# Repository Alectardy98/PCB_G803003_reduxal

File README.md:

# GH80-3003 Reduxal

Open-sourced Cherry MX PCB using the Pi Pico (RP2040) for the Cherry G80 3001 line of keyboards. Stock keyboards shipped originally with Cherry MY switches.

Original Placement measurements taken from other open-sourced PCB designs.
https://github.com/evyd13/gh80-series
https://github.com/Gacathon/Chili

## Production
Production files in the JLCPCB Folder

## Firmware
Qmk/Vial Firmware in the firmware folder

Use at your own risk.

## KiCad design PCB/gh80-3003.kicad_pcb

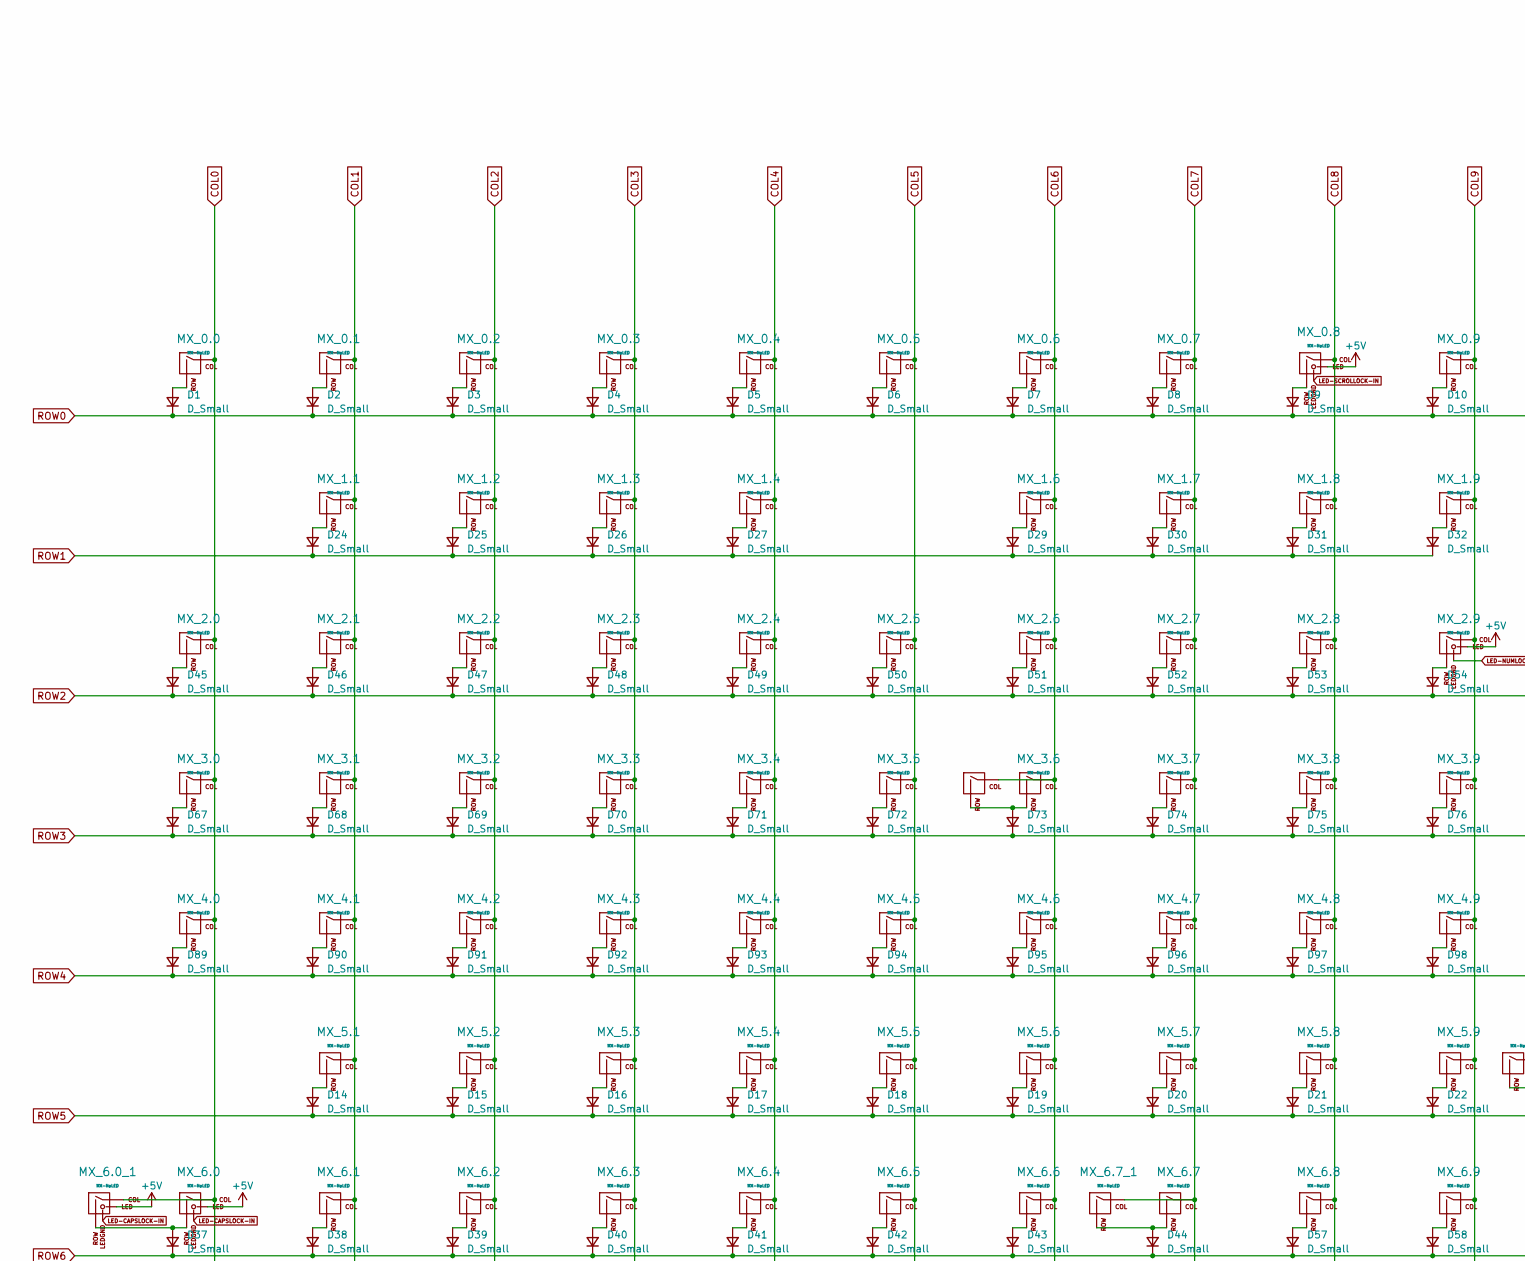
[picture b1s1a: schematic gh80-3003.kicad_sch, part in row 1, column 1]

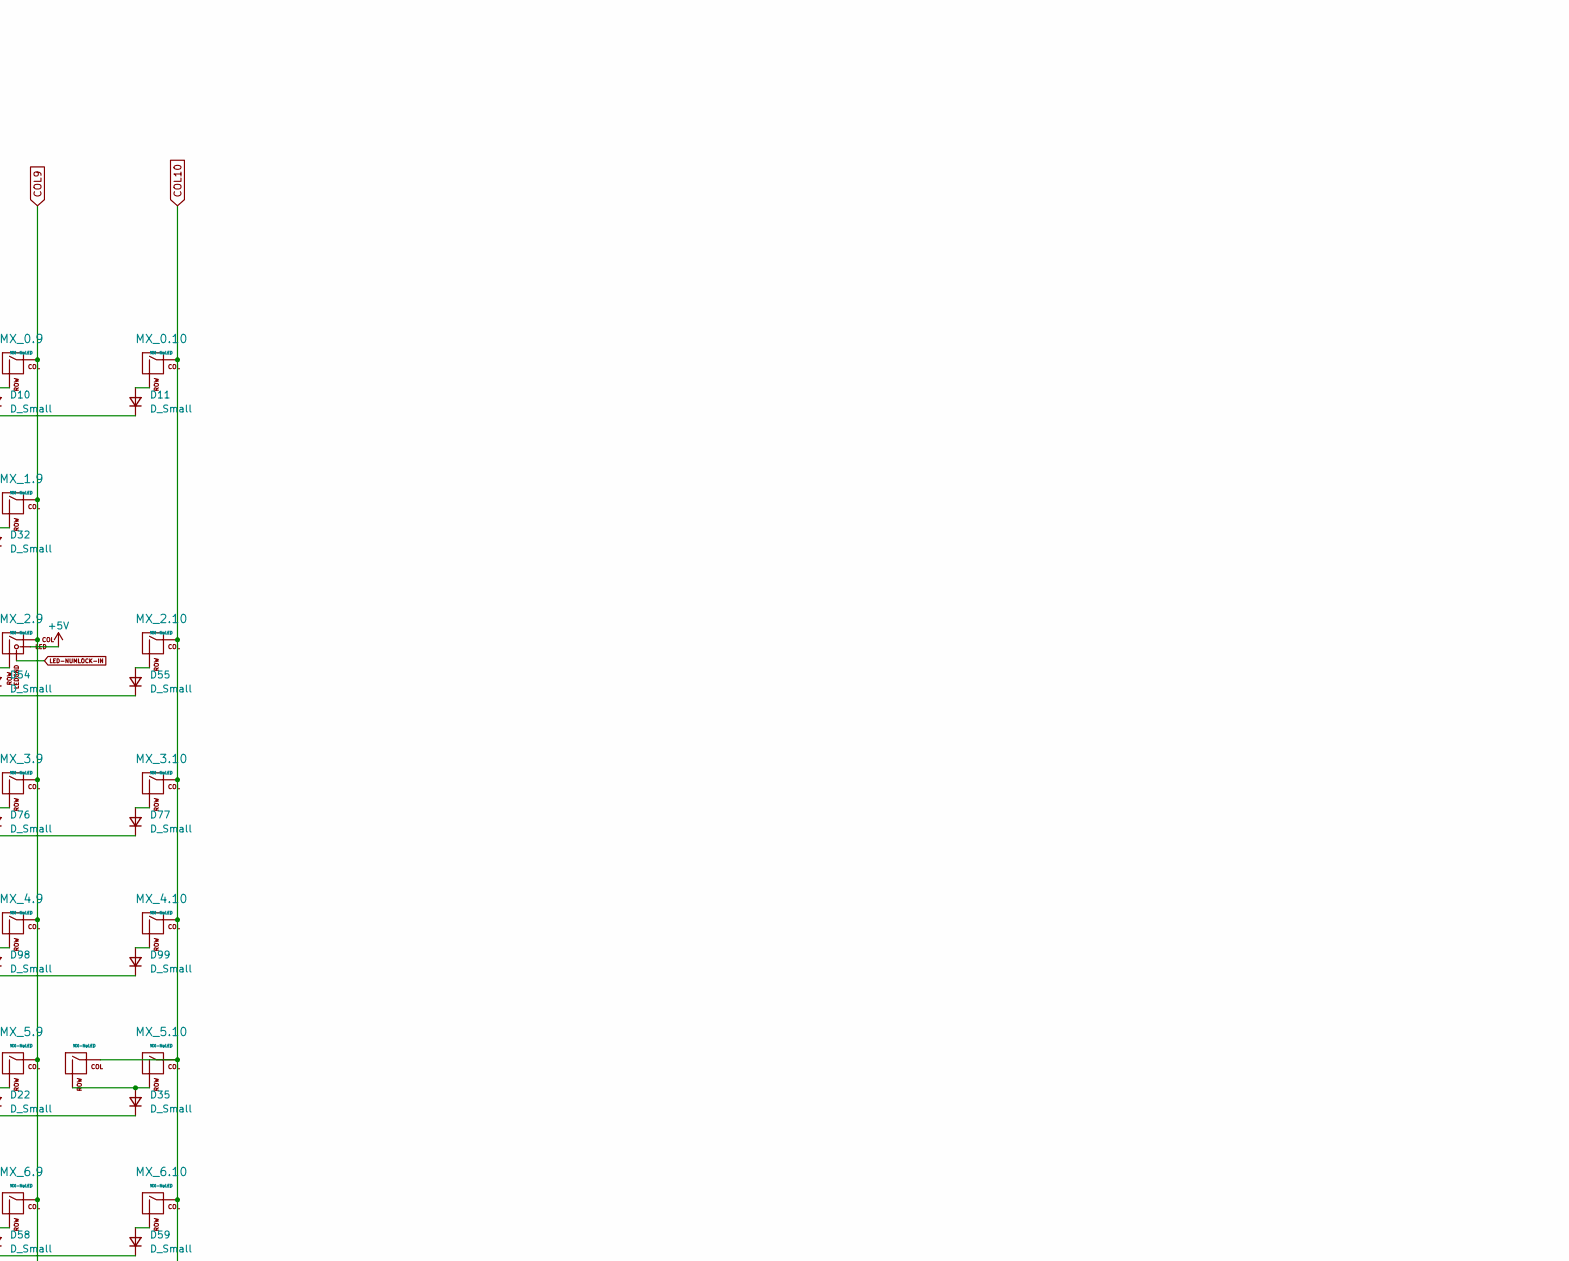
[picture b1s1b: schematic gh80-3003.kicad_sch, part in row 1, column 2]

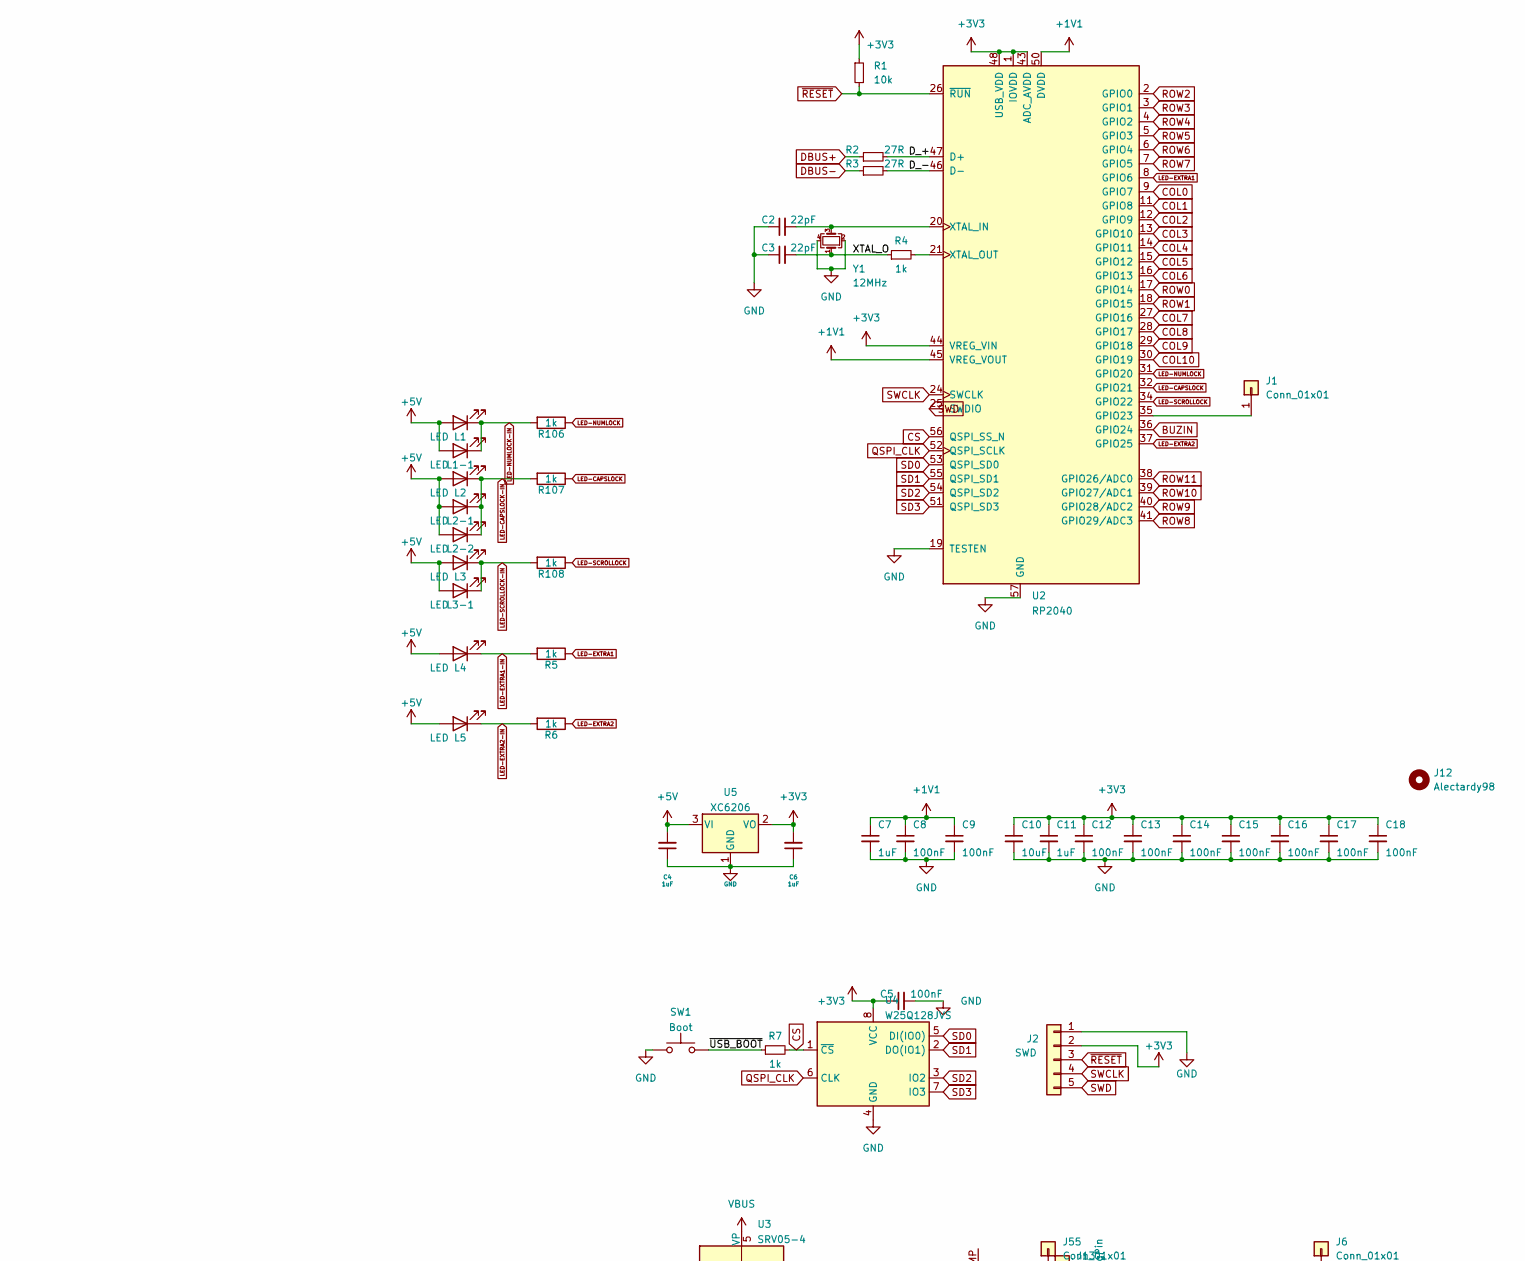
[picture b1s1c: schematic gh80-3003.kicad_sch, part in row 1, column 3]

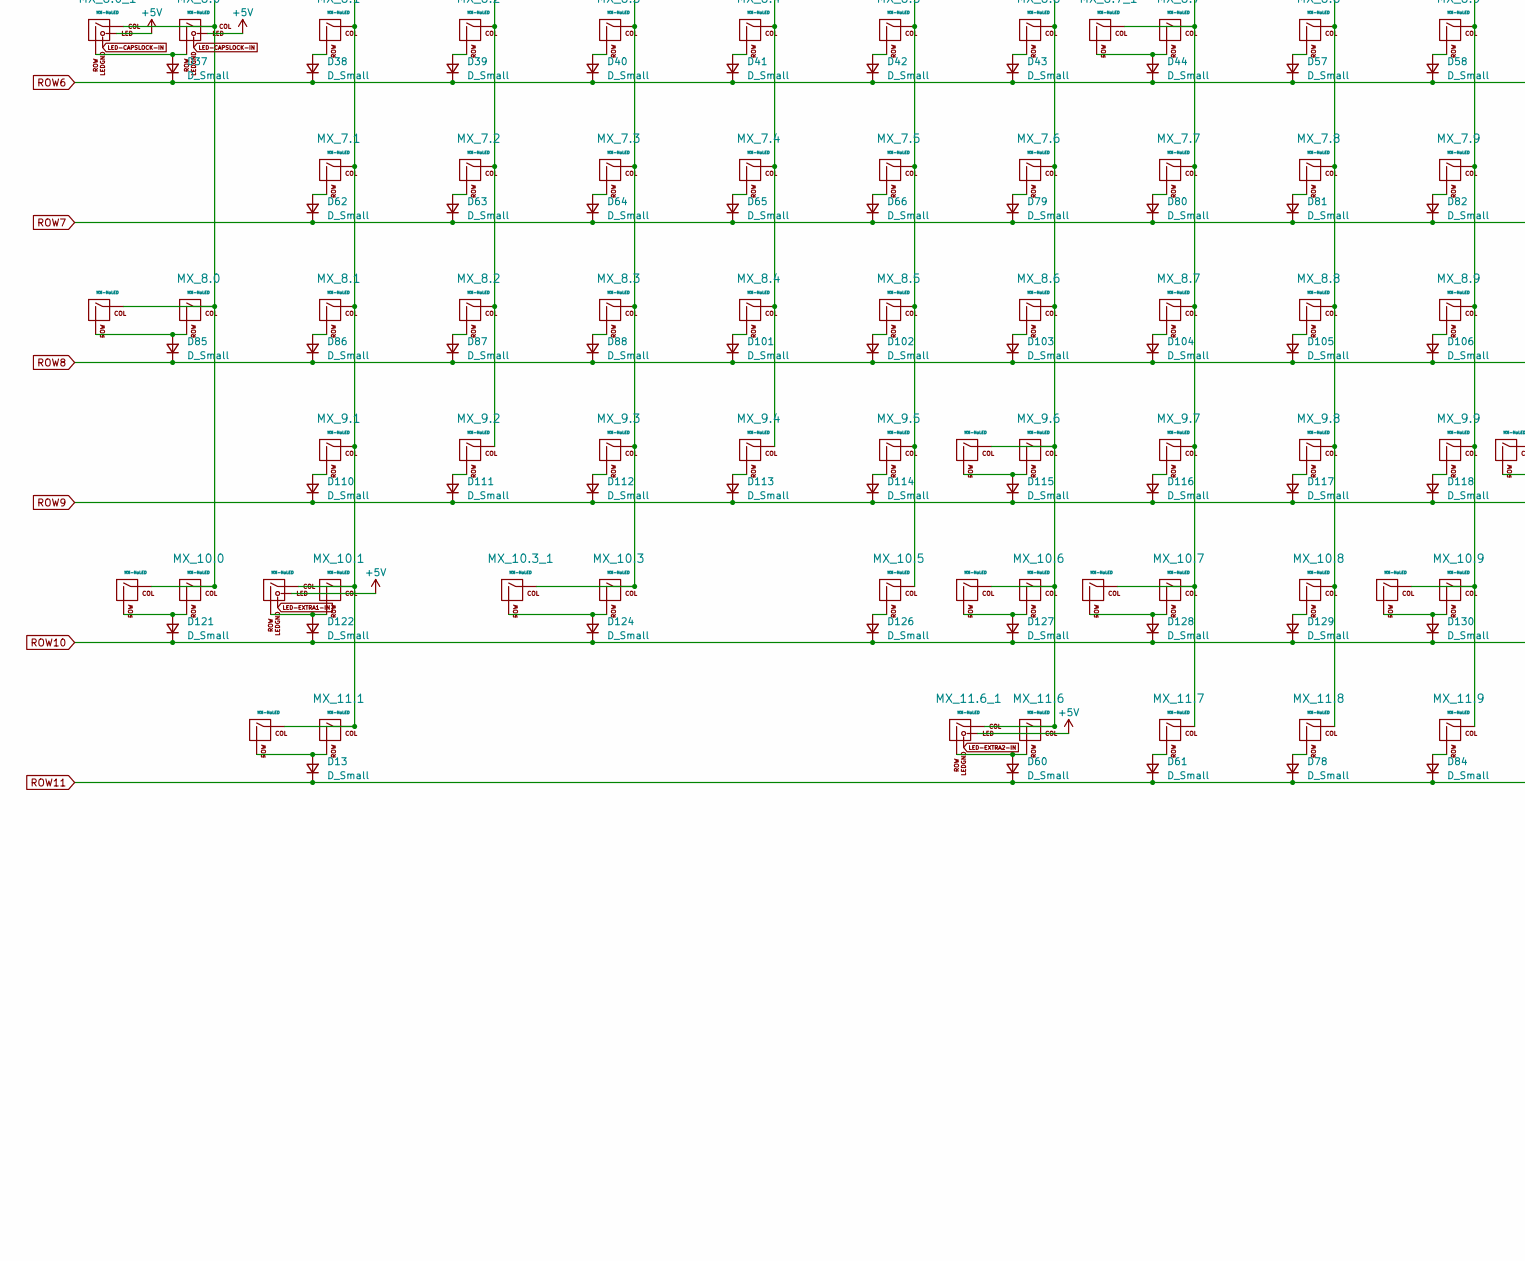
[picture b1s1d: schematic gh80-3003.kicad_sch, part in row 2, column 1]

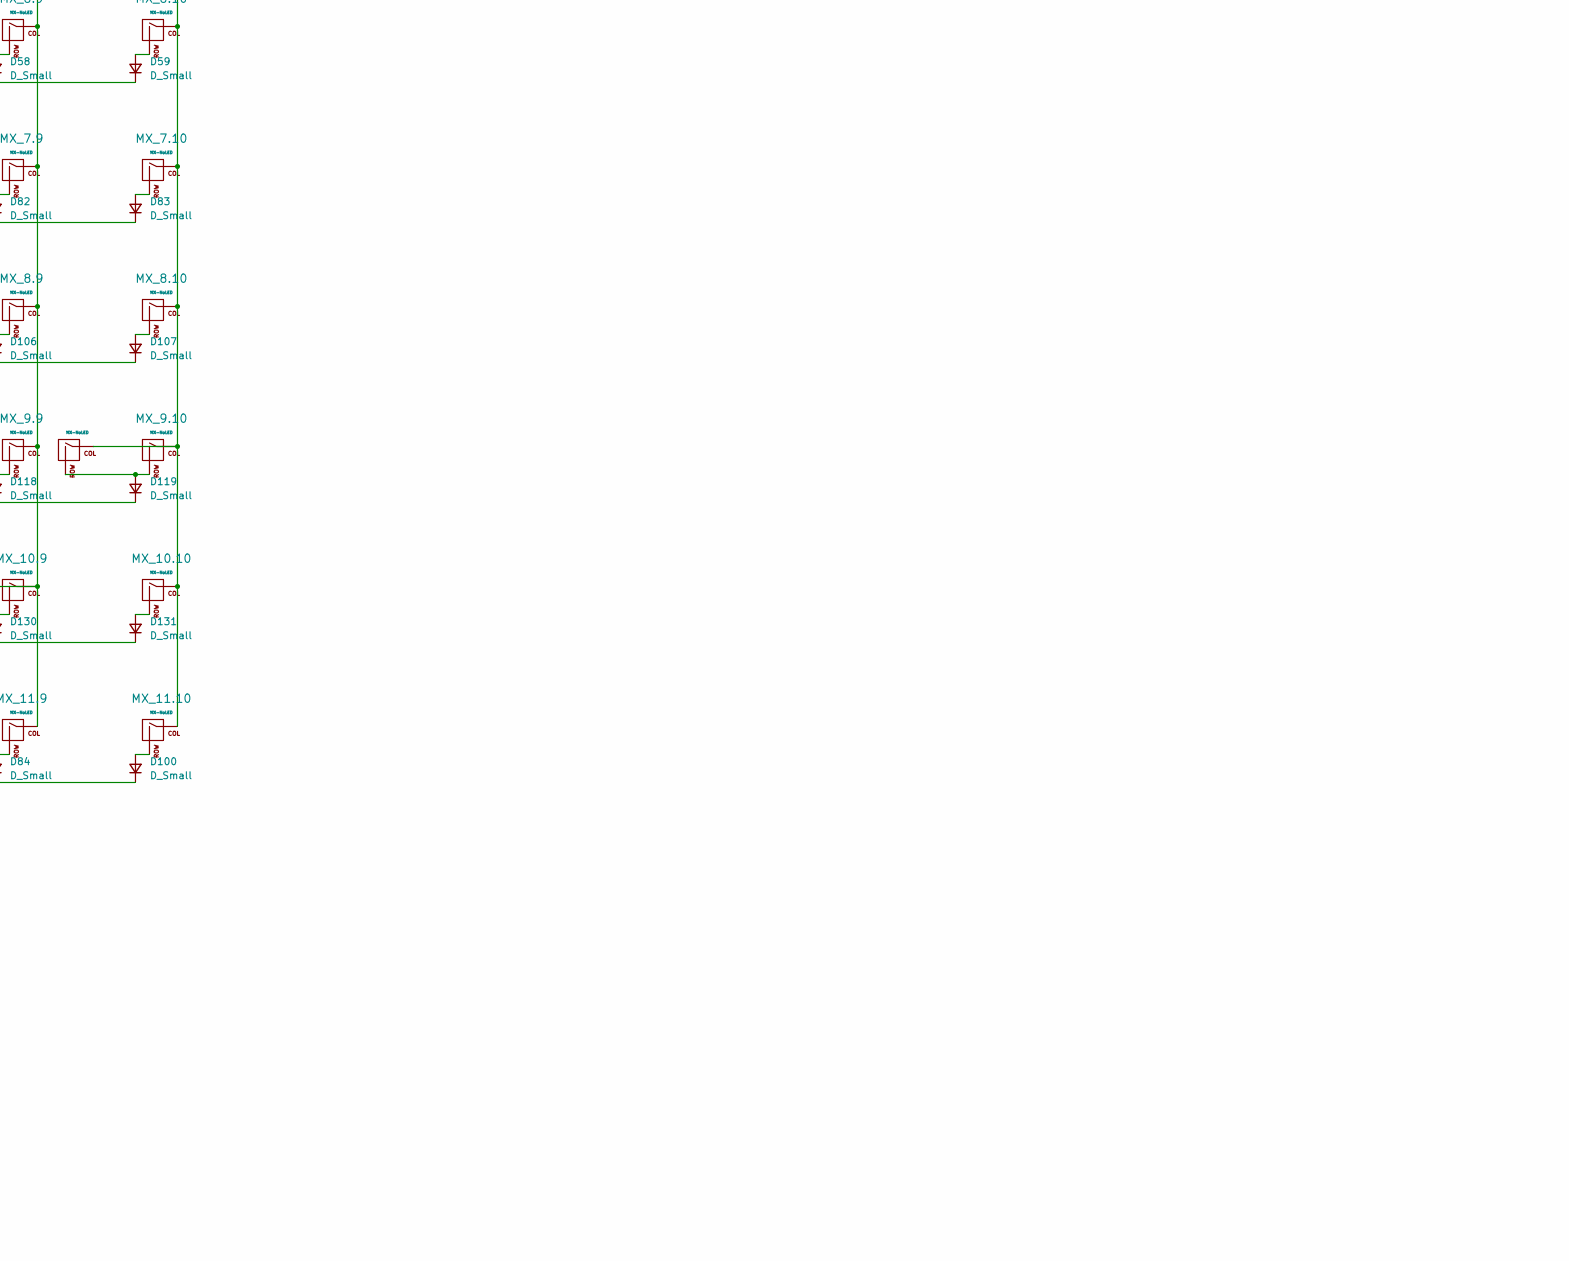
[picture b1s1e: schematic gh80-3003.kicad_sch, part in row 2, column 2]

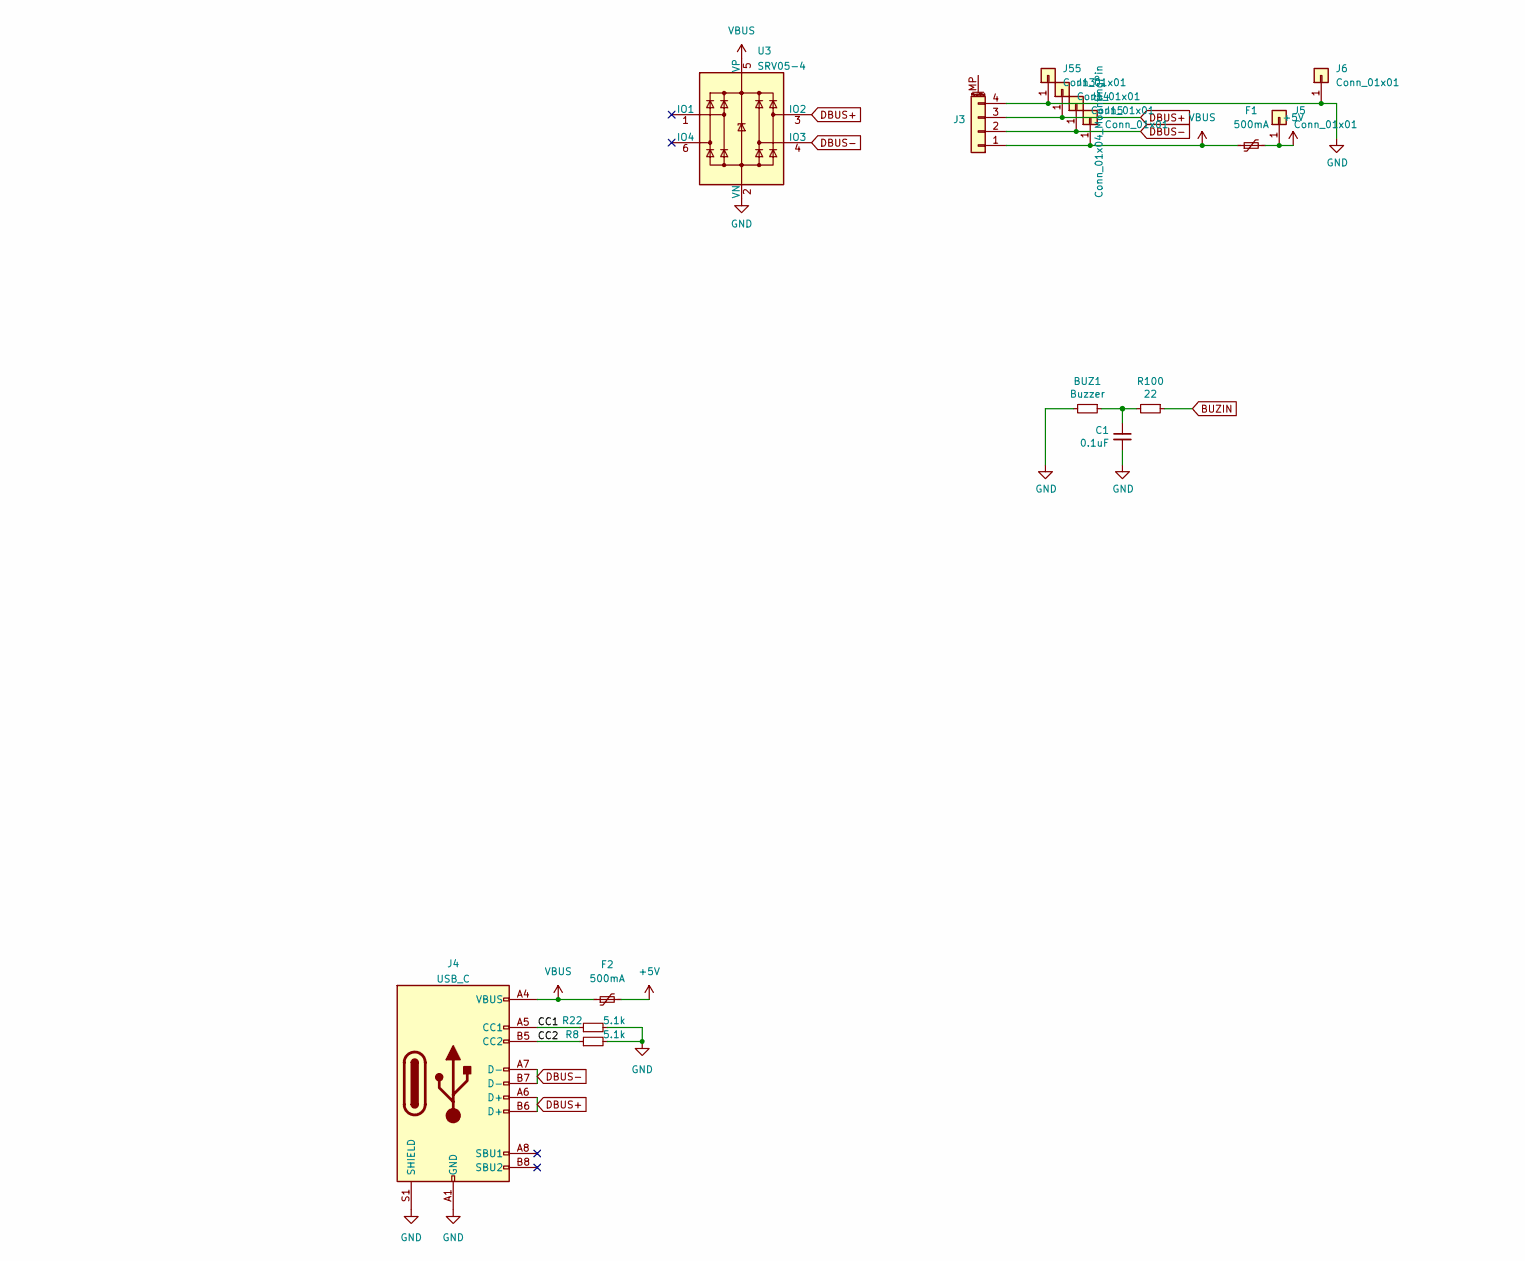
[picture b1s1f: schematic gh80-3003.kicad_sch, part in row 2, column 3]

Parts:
BUZ1: Buzzer; Buzzer_Mallory_AST1109MLTRQ
C1: 0.1uF; C_0805_2012Metric
C2, C3: 22pF; C_0402_1005Metric; LCSC C1555
C4, C6, C7, C11: 1uF; C_0402_1005Metric; LCSC C52923
C5, C8, C9, C12, C13, C14, C15, C16, C17, C18: 100nF; C_0402_1005Metric; LCSC C1525
C10: 10uF; C_0402_1005Metric; LCSC C15525
D1, D2, D3, D4, D5, D6, D7, D8, D9, D10, D11, D13, D14, D15, D16, D17, D18, D19, D20, D21, D22, D24, D25, D26, D27, D29, D30, D31, D32, D35, D37, D38, D39, D40, D41, D42, D43, D44, D45, D46, D47, D48, D49, D50, D51, D52, D53, D54, D55, D57, D58, D59, D60, D61, D62, D63, D64, D65, D66, D67, D68, D69, D70, D71, D72, D73, D74, D75, D76, D77, D78, D79, D80, D81, D82, D83, D84, D85, D86, D87, D88, D89, D90, D91, D92, D93, D94, D95, D96, D97, D98, D99, D100, D101, D102, D103, D104, D105, D106, D107, D110, D111, D112, D113, D114, D115, D116, D117, D118, D119, D121, D122, D124, D126, D127, D128, D129, D130, D131: D_Small; D_SOD-123
F1, F2: 500mA; Fuse_1206_3216Metric; LCSC C70076
J1, J5, J6, J13, J14, J15, J55: Conn_01x01; TestPoint_Plated_Hole_D2.0mm
J2: SWD; PinSocket_1x05_P2.54mm_Vertical
J3: Conn_01x04_MountingPin; JST_SH_SM04B-SRSS-TB_1x04-1MP_P1.00mm_Horizontal
J4: USB_C; USB_C_Receptacle_HRO_TYPE-C-31-M-12; LCSC C165948
J12: Alectardy98; Alectardy98101
L1, L2, L3: LED; LED_D3.0mm
L1-1, L2-1, L2-2, L3-1, L4, L5: LED; CHERRY_MX_LED
MX_0.0, MX_0.1, MX_0.2, MX_0.3, MX_0.4, MX_0.5, MX_0.6, MX_0.7, MX_0.9, MX_0.10, MX_1.1, MX_1.2, MX_1.3, MX_1.4, MX_1.6, MX_1.7, MX_1.8, MX_1.9, MX_2.0, MX_2.1, MX_2.2, MX_2.3, MX_2.4, MX_2.5, MX_2.6, MX_2.7, MX_2.8, MX_2.10, MX_3.0, MX_3.1, MX_3.2, MX_3.3, MX_3.4, MX_3.5, MX_3.6, MX_3.7, MX_3.8, MX_3.9, MX_3.10, MX_4.1, MX_4.2, MX_4.3, MX_4.4, MX_4.5, MX_4.6, MX_4.8, MX_4.9, MX_4.10, MX_5.1, MX_5.2, MX_5.3, MX_5.4, MX_5.5, MX_5.6, MX_5.7, MX_5.8, MX_5.9, MX_5.10, MX_6.1, MX_6.2, MX_6.3, MX_6.4, MX_6.5, MX_6.6, MX_6.8, MX_6.9, MX_6.10, MX_7.1, MX_7.2, MX_7.3, MX_7.4, MX_7.5, MX_7.6, MX_7.7, MX_7.8, MX_7.9, MX_7.10, MX_8.1, MX_8.2, MX_8.3, MX_8.4, MX_8.5, MX_8.6, MX_8.7, MX_8.8, MX_8.9, MX_8.10, MX_9.1, MX_9.2, MX_9.3, MX_9.4, MX_9.5, MX_9.7, MX_9.8, MX_9.9, MX_9.10, MX_10.8, MX_10.9, MX_10.10, MX_11.7, MX_11.8, MX_11.9, MX_11.10: MX-NoLED; MXOnly-1U-NoLED
MX_0.8, MX_2.9, MX_10.1_1, MX_11.6_1: MX-NoLED; MXOnly-1U
MX_3.6_1, MX_10.9_1: MX-NoLED; MXOnly-2U-NoLED
MX_4.0, MX_4.7, MX_10.0_1, MX_10.6_1, MX_10.7_1, MX_11.1_1: MX-NoLED; MXOnly-1.5U-NoLED
MX_5.10_1, MX_9.10_1: MX-NoLED; MXOnly-2U-VerticalStabilizers-NoLED
MX_6.0: MX-NoLED; MXOnly-1.75U
MX_6.0_1: MX-NoLED; MXOnly-1.25U
MX_6.7, MX_8.0_1: MX-NoLED; MXOnly-2.25U-NoLED
MX_6.7_1: MX-NoLED; MXOnly-ISO-ReversedStabilizers-NoLED
MX_8.0, MX_10.0, MX_10.1, MX_10.5, MX_10.6, MX_10.7, MX_11.1, MX_11.6: MX-NoLED; MXOnly-1.25U-NoLED
MX_9.6: MX-NoLED; MXOnly-1.75U-NoLED
MX_9.6_1: MX-NoLED; MXOnly-2.75U-NoLED
MX_10.3: MX-NoLED; MXOnly-6.25U-NoLED
MX_10.3_1: MX-NoLED; MXOnly-7U-NoLED
R1: 10k; R_0402_1005Metric; LCSC C25744
R2, R3: 27R; R_0603_1608Metric; LCSC C25190
R4, R7: 1k; R_0402_1005Metric; LCSC C11702
R5, R6, R106, R107, R108: 1k; R_0805_2012Metric
R8, R22: 5.1k; R_0402_1005Metric; LCSC C25905
R100: 22; R_0805_2012Metric
SW1: Boot; PinSocket_1x02_P2.54mm_Vertical
U2: RP2040; RP2040-QFN-56; LCSC C2040
U3: SRV05-4; SOT-23-6-routable; LCSC C85364
U4: W25Q128JVS; SOIC-8_5.23x5.23mm_P1.27mm; LCSC C97521
U5: XC6206; SOT-23; LCSC C5446
Y1: 12MHz; Crystal_SMD_3225-4Pin_3.2x2.5mm; LCSC C9002

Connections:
+1V1: C7.1, C8.1, C9.1, U2.23 (DVDD), U2.45 (VREG_VOUT), U2.50 (DVDD)
+3V3: C5.1, C6.2, C10.1, C11.1, C12.1, C13.1, C14.1, C15.1, C16.1, C17.1, C18.1, J2.2, R1.1, U2.1 (IOVDD), U2.10 (IOVDD), U2.22 (IOVDD), U2.33 (IOVDD), U2.42 (IOVDD), U2.43 (ADC_AVDD), U2.44 (VREG_VIN), U2.48 (USB_VDD), U2.49 (IOVDD), U4.8 (VCC), U5.2 (VO)
+5V: C4.2, F1.2, F2.2, J5.1, L1.2 (A), L1-1.2 (A), L2.2 (A), L2-1.2 (A), L2-2.2 (A), L3.2 (A), L3-1.2 (A), L4.2 (A), L5.2 (A), MX_0.8.3 (LED), MX_2.9.3 (LED), MX_6.0.3 (LED), MX_6.0_1.3 (LED), MX_10.1_1.3 (LED), MX_11.6_1.3 (LED), U5.3 (VI)
/CC1: J4.A5 (CC1), R22.1
/CC2: J4.B5 (CC2), R8.1
/D_+: R2.2, U2.47 (D+)
/D_-: R3.2, U2.46 (D-)
/XTAL_O: C3.2, R4.1, Y1.1
/~USB_BOOT: R7.1, SW1.2
BUZIN: R100.1, U2.36 (GPIO24)
COL0: MX_0.0.1 (COL), MX_2.0.1 (COL), MX_3.0.1 (COL), MX_4.0.1 (COL), MX_6.0.1 (COL), MX_6.0_1.1 (COL), MX_8.0.1 (COL), MX_8.0_1.1 (COL), MX_10.0.1 (COL), MX_10.0_1.1 (COL), U2.9 (GPIO7)
COL1: MX_0.1.1 (COL), MX_1.1.1 (COL), MX_2.1.1 (COL), MX_3.1.1 (COL), MX_4.1.1 (COL), MX_5.1.1 (COL), MX_6.1.1 (COL), MX_7.1.1 (COL), MX_8.1.1 (COL), MX_9.1.1 (COL), MX_10.1.1 (COL), MX_10.1_1.1 (COL), MX_11.1.1 (COL), MX_11.1_1.1 (COL), U2.11 (GPIO8)
COL2: MX_0.2.1 (COL), MX_1.2.1 (COL), MX_2.2.1 (COL), MX_3.2.1 (COL), MX_4.2.1 (COL), MX_5.2.1 (COL), MX_6.2.1 (COL), MX_7.2.1 (COL), MX_8.2.1 (COL), MX_9.2.1 (COL), U2.12 (GPIO9)
COL3: MX_0.3.1 (COL), MX_1.3.1 (COL), MX_2.3.1 (COL), MX_3.3.1 (COL), MX_4.3.1 (COL), MX_5.3.1 (COL), MX_6.3.1 (COL), MX_7.3.1 (COL), MX_8.3.1 (COL), MX_9.3.1 (COL), MX_10.3.1 (COL), MX_10.3_1.1 (COL), U2.13 (GPIO10)
COL4: MX_0.4.1 (COL), MX_1.4.1 (COL), MX_2.4.1 (COL), MX_3.4.1 (COL), MX_4.4.1 (COL), MX_5.4.1 (COL), MX_6.4.1 (COL), MX_7.4.1 (COL), MX_8.4.1 (COL), MX_9.4.1 (COL), U2.14 (GPIO11)
COL5: MX_0.5.1 (COL), MX_2.5.1 (COL), MX_3.5.1 (COL), MX_4.5.1 (COL), MX_5.5.1 (COL), MX_6.5.1 (COL), MX_7.5.1 (COL), MX_8.5.1 (COL), MX_9.5.1 (COL), MX_10.5.1 (COL), U2.15 (GPIO12)
COL6: MX_0.6.1 (COL), MX_1.6.1 (COL), MX_2.6.1 (COL), MX_3.6.1 (COL), MX_3.6_1.1 (COL), MX_4.6.1 (COL), MX_5.6.1 (COL), MX_6.6.1 (COL), MX_7.6.1 (COL), MX_8.6.1 (COL), MX_9.6.1 (COL), MX_9.6_1.1 (COL), MX_10.6.1 (COL), MX_10.6_1.1 (COL), MX_11.6.1 (COL), MX_11.6_1.1 (COL), U2.16 (GPIO13)
COL7: MX_0.7.1 (COL), MX_1.7.1 (COL), MX_2.7.1 (COL), MX_3.7.1 (COL), MX_4.7.1 (COL), MX_5.7.1 (COL), MX_6.7.1 (COL), MX_6.7_1.1 (COL), MX_7.7.1 (COL), MX_8.7.1 (COL), MX_9.7.1 (COL), MX_10.7.1 (COL), MX_10.7_1.1 (COL), MX_11.7.1 (COL), U2.27 (GPIO16)
COL8: MX_0.8.1 (COL), MX_1.8.1 (COL), MX_2.8.1 (COL), MX_3.8.1 (COL), MX_4.8.1 (COL), MX_5.8.1 (COL), MX_6.8.1 (COL), MX_7.8.1 (COL), MX_8.8.1 (COL), MX_9.8.1 (COL), MX_10.8.1 (COL), MX_11.8.1 (COL), U2.28 (GPIO17)
COL9: MX_0.9.1 (COL), MX_1.9.1 (COL), MX_2.9.1 (COL), MX_3.9.1 (COL), MX_4.9.1 (COL), MX_5.9.1 (COL), MX_6.9.1 (COL), MX_7.9.1 (COL), MX_8.9.1 (COL), MX_9.9.1 (COL), MX_10.9.1 (COL), MX_10.9_1.1 (COL), MX_11.9.1 (COL), U2.29 (GPIO18)
COL10: MX_0.10.1 (COL), MX_2.10.1 (COL), MX_3.10.1 (COL), MX_4.10.1 (COL), MX_5.10.1 (COL), MX_5.10_1.1 (COL), MX_6.10.1 (COL), MX_7.10.1 (COL), MX_8.10.1 (COL), MX_9.10.1 (COL), MX_9.10_1.1 (COL), MX_10.10.1 (COL), MX_11.10.1 (COL), U2.30 (GPIO19)
CS: R7.2, U2.56 (QSPI_SS_N), U4.1 (~CS)
DBUS+: J3.3, J4.A6 (D+), J4.B6 (D+), J13.1, R2.1, U3.3 (IO2)
DBUS-: J3.2, J4.A7 (D-), J4.B7 (D-), J14.1, R3.1, U3.4 (IO3)
GND: BUZ1.2, C1.2, C2.1, C3.1, C4.1, C5.2, C6.1, C7.2, C8.2, C9.2, C10.2, C11.2, C12.2, C13.2, C14.2, C15.2, C16.2, C17.2, C18.2, J2.1, J3.4, J4.A1 (GND), J4.A12 (GND), J4.B1 (GND), J4.B12 (GND), J4.S1 (SHIELD), J6.1, J55.1, R8.2, R22.2, SW1.1, U2.19 (TESTEN), U2.57 (GND), U3.2 (VN), U4.4 (GND), U5.1 (GND), Y1.2, Y1.4
LED-CAPSLOCK: R107.1, U2.32 (GPIO21)
LED-CAPSLOCK-IN: L2.1 (K), L2-1.1 (K), L2-2.1 (K), MX_6.0.4 (LEDGND), MX_6.0_1.4 (LEDGND), R107.2
LED-EXTRA1: R5.1, U2.8 (GPIO6)
LED-EXTRA1-IN: L4.1 (K), MX_10.1_1.4 (LEDGND), R5.2
LED-EXTRA2: R6.1, U2.37 (GPIO25)
LED-EXTRA2-IN: L5.1 (K), MX_11.6_1.4 (LEDGND), R6.2
LED-NUMLOCK: R106.1, U2.31 (GPIO20)
LED-NUMLOCK-IN: L1.1 (K), L1-1.1 (K), MX_2.9.4 (LEDGND), R106.2
LED-SCROLLOCK: R108.1, U2.34 (GPIO22)
LED-SCROLLOCK-IN: L3.1 (K), L3-1.1 (K), MX_0.8.4 (LEDGND), R108.2
unnamed: BUZ1.1, C1.1, R100.2
unnamed: D1.2 (A), MX_0.0.2 (ROW)
unnamed: D2.2 (A), MX_0.1.2 (ROW)
unnamed: D3.2 (A), MX_0.2.2 (ROW)
unnamed: D4.2 (A), MX_0.3.2 (ROW)
unnamed: D5.2 (A), MX_0.4.2 (ROW)
unnamed: D6.2 (A), MX_0.5.2 (ROW)
unnamed: D7.2 (A), MX_0.6.2 (ROW)
unnamed: D8.2 (A), MX_0.7.2 (ROW)
unnamed: D9.2 (A), MX_0.8.2 (ROW)
unnamed: D10.2 (A), MX_0.9.2 (ROW)
unnamed: D11.2 (A), MX_0.10.2 (ROW)
unnamed: D13.2 (A), MX_11.1.2 (ROW), MX_11.1_1.2 (ROW)
unnamed: D14.2 (A), MX_5.1.2 (ROW)
unnamed: D15.2 (A), MX_5.2.2 (ROW)
unnamed: D16.2 (A), MX_5.3.2 (ROW)
unnamed: D17.2 (A), MX_5.4.2 (ROW)
unnamed: D18.2 (A), MX_5.5.2 (ROW)
unnamed: D19.2 (A), MX_5.6.2 (ROW)
unnamed: D20.2 (A), MX_5.7.2 (ROW)
unnamed: D21.2 (A), MX_5.8.2 (ROW)
unnamed: D22.2 (A), MX_5.9.2 (ROW)
unnamed: D24.2 (A), MX_1.1.2 (ROW)
unnamed: D25.2 (A), MX_1.2.2 (ROW)
unnamed: D26.2 (A), MX_1.3.2 (ROW)
unnamed: D27.2 (A), MX_1.4.2 (ROW)
unnamed: D29.2 (A), MX_1.6.2 (ROW)
unnamed: D30.2 (A), MX_1.7.2 (ROW)
unnamed: D31.2 (A), MX_1.8.2 (ROW)
unnamed: D32.2 (A), MX_1.9.2 (ROW)
unnamed: D35.2 (A), MX_5.10.2 (ROW), MX_5.10_1.2 (ROW)
unnamed: D37.2 (A), MX_6.0.2 (ROW), MX_6.0_1.2 (ROW)
unnamed: D38.2 (A), MX_6.1.2 (ROW)
unnamed: D39.2 (A), MX_6.2.2 (ROW)
unnamed: D40.2 (A), MX_6.3.2 (ROW)
unnamed: D41.2 (A), MX_6.4.2 (ROW)
unnamed: D42.2 (A), MX_6.5.2 (ROW)
unnamed: D43.2 (A), MX_6.6.2 (ROW)
unnamed: D44.2 (A), MX_6.7.2 (ROW), MX_6.7_1.2 (ROW)
unnamed: D45.2 (A), MX_2.0.2 (ROW)
unnamed: D46.2 (A), MX_2.1.2 (ROW)
unnamed: D47.2 (A), MX_2.2.2 (ROW)
unnamed: D48.2 (A), MX_2.3.2 (ROW)
unnamed: D49.2 (A), MX_2.4.2 (ROW)
unnamed: D50.2 (A), MX_2.5.2 (ROW)
unnamed: D51.2 (A), MX_2.6.2 (ROW)
unnamed: D52.2 (A), MX_2.7.2 (ROW)
unnamed: D53.2 (A), MX_2.8.2 (ROW)
unnamed: D54.2 (A), MX_2.9.2 (ROW)
unnamed: D55.2 (A), MX_2.10.2 (ROW)
unnamed: D57.2 (A), MX_6.8.2 (ROW)
unnamed: D58.2 (A), MX_6.9.2 (ROW)
unnamed: D59.2 (A), MX_6.10.2 (ROW)
unnamed: D60.2 (A), MX_11.6.2 (ROW), MX_11.6_1.2 (ROW)
unnamed: D61.2 (A), MX_11.7.2 (ROW)
unnamed: D62.2 (A), MX_7.1.2 (ROW)
unnamed: D63.2 (A), MX_7.2.2 (ROW)
unnamed: D64.2 (A), MX_7.3.2 (ROW)
unnamed: D65.2 (A), MX_7.4.2 (ROW)
unnamed: D66.2 (A), MX_7.5.2 (ROW)
unnamed: D67.2 (A), MX_3.0.2 (ROW)
unnamed: D68.2 (A), MX_3.1.2 (ROW)
unnamed: D69.2 (A), MX_3.2.2 (ROW)
unnamed: D70.2 (A), MX_3.3.2 (ROW)
unnamed: D71.2 (A), MX_3.4.2 (ROW)
unnamed: D72.2 (A), MX_3.5.2 (ROW)
unnamed: D73.2 (A), MX_3.6.2 (ROW), MX_3.6_1.2 (ROW)
unnamed: D74.2 (A), MX_3.7.2 (ROW)
unnamed: D75.2 (A), MX_3.8.2 (ROW)
unnamed: D76.2 (A), MX_3.9.2 (ROW)
unnamed: D77.2 (A), MX_3.10.2 (ROW)
unnamed: D78.2 (A), MX_11.8.2 (ROW)
unnamed: D79.2 (A), MX_7.6.2 (ROW)
unnamed: D80.2 (A), MX_7.7.2 (ROW)
unnamed: D81.2 (A), MX_7.8.2 (ROW)
unnamed: D82.2 (A), MX_7.9.2 (ROW)
unnamed: D83.2 (A), MX_7.10.2 (ROW)
unnamed: D84.2 (A), MX_11.9.2 (ROW)
unnamed: D85.2 (A), MX_8.0.2 (ROW), MX_8.0_1.2 (ROW)
unnamed: D86.2 (A), MX_8.1.2 (ROW)
unnamed: D87.2 (A), MX_8.2.2 (ROW)
unnamed: D88.2 (A), MX_8.3.2 (ROW)
unnamed: D89.2 (A), MX_4.0.2 (ROW)
unnamed: D90.2 (A), MX_4.1.2 (ROW)
unnamed: D91.2 (A), MX_4.2.2 (ROW)
unnamed: D92.2 (A), MX_4.3.2 (ROW)
unnamed: D93.2 (A), MX_4.4.2 (ROW)
unnamed: D94.2 (A), MX_4.5.2 (ROW)
unnamed: D95.2 (A), MX_4.6.2 (ROW)
unnamed: D96.2 (A), MX_4.7.2 (ROW)
unnamed: D97.2 (A), MX_4.8.2 (ROW)
unnamed: D98.2 (A), MX_4.9.2 (ROW)
unnamed: D99.2 (A), MX_4.10.2 (ROW)
unnamed: D100.2 (A), MX_11.10.2 (ROW)
unnamed: D101.2 (A), MX_8.4.2 (ROW)
unnamed: D102.2 (A), MX_8.5.2 (ROW)
unnamed: D103.2 (A), MX_8.6.2 (ROW)
unnamed: D104.2 (A), MX_8.7.2 (ROW)
unnamed: D105.2 (A), MX_8.8.2 (ROW)
unnamed: D106.2 (A), MX_8.9.2 (ROW)
unnamed: D107.2 (A), MX_8.10.2 (ROW)
unnamed: D110.2 (A), MX_9.1.2 (ROW)
unnamed: D111.2 (A), MX_9.2.2 (ROW)
unnamed: D112.2 (A), MX_9.3.2 (ROW)
unnamed: D113.2 (A), MX_9.4.2 (ROW)
unnamed: D114.2 (A), MX_9.5.2 (ROW)
unnamed: D115.2 (A), MX_9.6.2 (ROW), MX_9.6_1.2 (ROW)
unnamed: D116.2 (A), MX_9.7.2 (ROW)
unnamed: D117.2 (A), MX_9.8.2 (ROW)
unnamed: D118.2 (A), MX_9.9.2 (ROW)
unnamed: D119.2 (A), MX_9.10.2 (ROW), MX_9.10_1.2 (ROW)
unnamed: D121.2 (A), MX_10.0.2 (ROW), MX_10.0_1.2 (ROW)
unnamed: D122.2 (A), MX_10.1.2 (ROW), MX_10.1_1.2 (ROW)
unnamed: D124.2 (A), MX_10.3.2 (ROW), MX_10.3_1.2 (ROW)
unnamed: D126.2 (A), MX_10.5.2 (ROW)
unnamed: D127.2 (A), MX_10.6.2 (ROW), MX_10.6_1.2 (ROW)
unnamed: D128.2 (A), MX_10.7.2 (ROW), MX_10.7_1.2 (ROW)
unnamed: D129.2 (A), MX_10.8.2 (ROW)
unnamed: D130.2 (A), MX_10.9.2 (ROW), MX_10.9_1.2 (ROW)
unnamed: D131.2 (A), MX_10.10.2 (ROW)
unnamed: J1.1, U2.35 (GPIO23)
unnamed: C2.2, U2.20 (XTAL_IN), Y1.3
unnamed: R4.2, U2.21 (XTAL_OUT)
QSPI_CLK: U2.52 (QSPI_SCLK), U4.6 (CLK)
ROW0: D1.1 (K), D2.1 (K), D3.1 (K), D4.1 (K), D5.1 (K), D6.1 (K), D7.1 (K), D8.1 (K), D9.1 (K), D10.1 (K), D11.1 (K), U2.17 (GPIO14)
ROW1: D24.1 (K), D25.1 (K), D26.1 (K), D27.1 (K), D29.1 (K), D30.1 (K), D31.1 (K), D32.1 (K), U2.18 (GPIO15)
ROW2: D45.1 (K), D46.1 (K), D47.1 (K), D48.1 (K), D49.1 (K), D50.1 (K), D51.1 (K), D52.1 (K), D53.1 (K), D54.1 (K), D55.1 (K), U2.2 (GPIO0)
ROW3: D67.1 (K), D68.1 (K), D69.1 (K), D70.1 (K), D71.1 (K), D72.1 (K), D73.1 (K), D74.1 (K), D75.1 (K), D76.1 (K), D77.1 (K), U2.3 (GPIO1)
ROW4: D89.1 (K), D90.1 (K), D91.1 (K), D92.1 (K), D93.1 (K), D94.1 (K), D95.1 (K), D96.1 (K), D97.1 (K), D98.1 (K), D99.1 (K), U2.4 (GPIO2)
ROW5: D14.1 (K), D15.1 (K), D16.1 (K), D17.1 (K), D18.1 (K), D19.1 (K), D20.1 (K), D21.1 (K), D22.1 (K), D35.1 (K), U2.5 (GPIO3)
ROW6: D37.1 (K), D38.1 (K), D39.1 (K), D40.1 (K), D41.1 (K), D42.1 (K), D43.1 (K), D44.1 (K), D57.1 (K), D58.1 (K), D59.1 (K), U2.6 (GPIO4)
ROW7: D62.1 (K), D63.1 (K), D64.1 (K), D65.1 (K), D66.1 (K), D79.1 (K), D80.1 (K), D81.1 (K), D82.1 (K), D83.1 (K), U2.7 (GPIO5)
ROW8: D85.1 (K), D86.1 (K), D87.1 (K), D88.1 (K), D101.1 (K), D102.1 (K), D103.1 (K), D104.1 (K), D105.1 (K), D106.1 (K), D107.1 (K), U2.41 (GPIO29/ADC3)
ROW9: D110.1 (K), D111.1 (K), D112.1 (K), D113.1 (K), D114.1 (K), D115.1 (K), D116.1 (K), D117.1 (K), D118.1 (K), D119.1 (K), U2.40 (GPIO28/ADC2)
ROW10: D121.1 (K), D122.1 (K), D124.1 (K), D126.1 (K), D127.1 (K), D128.1 (K), D129.1 (K), D130.1 (K), D131.1 (K), U2.39 (GPIO27/ADC1)
ROW11: D13.1 (K), D60.1 (K), D61.1 (K), D78.1 (K), D84.1 (K), D100.1 (K), U2.38 (GPIO26/ADC0)
SD0: U2.53 (QSPI_SD0), U4.5 (DI(IO0))
SD1: U2.55 (QSPI_SD1), U4.2 (DO(IO1))
SD2: U2.54 (QSPI_SD2), U4.3 (IO2)
SD3: U2.51 (QSPI_SD3), U4.7 (IO3)
SWCLK: J2.4, U2.24 (SWCLK)
SWD: J2.5, U2.25 (SWDIO)
VBUS: F1.1, F2.1, J3.1, J4.A4 (VBUS), J4.A9 (VBUS), J4.B4 (VBUS), J4.B9 (VBUS), J15.1, U3.5 (VP)
~RESET: J2.3, R1.2, U2.26 (~RUN)

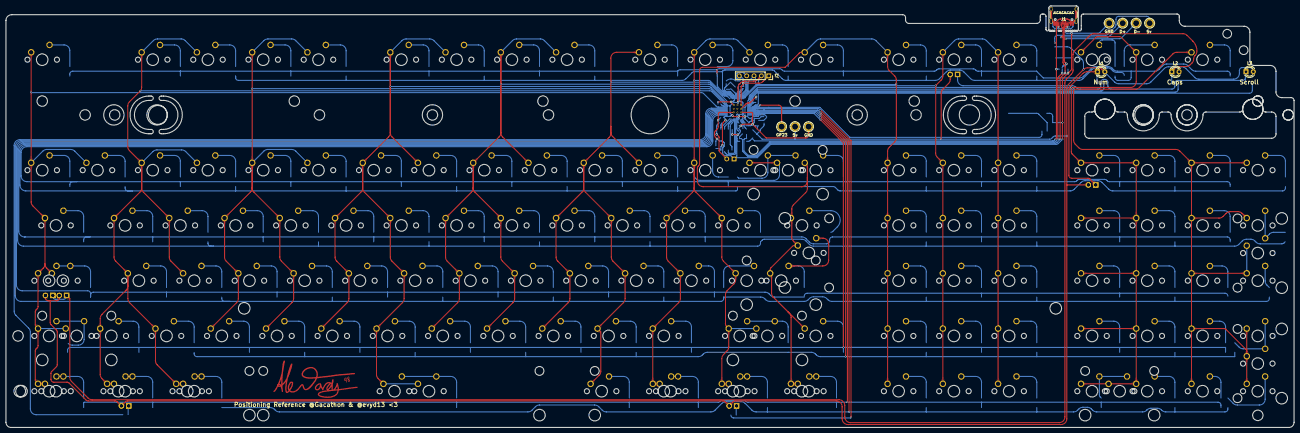
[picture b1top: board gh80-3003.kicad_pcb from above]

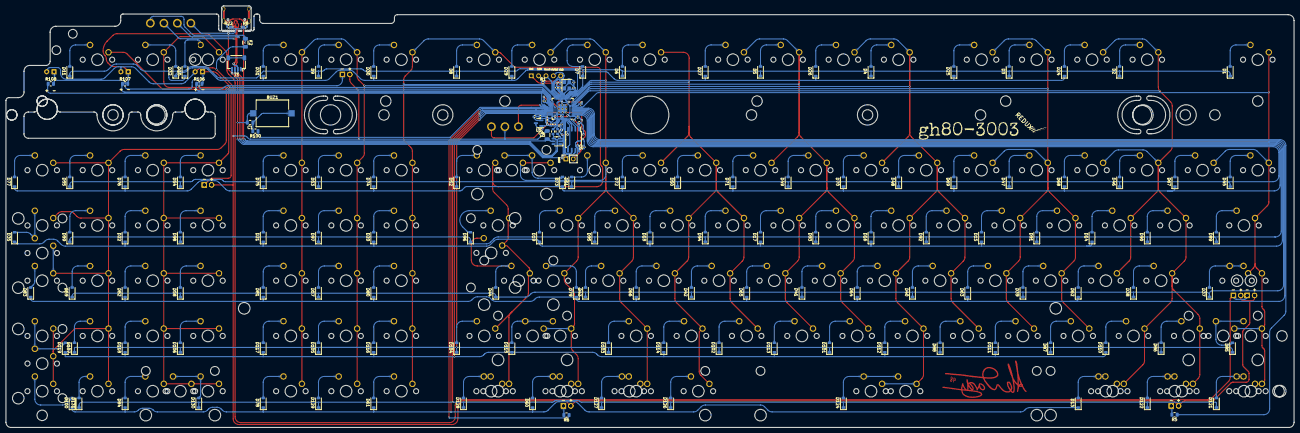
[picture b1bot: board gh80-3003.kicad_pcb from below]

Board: 2 copper layers, 444.1 x 145.3 mm, 316 parts (160 on the bottom side), 179 nets.

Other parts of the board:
L5#2, L5#3, L5#4: LED; CHERRY_MX_LED

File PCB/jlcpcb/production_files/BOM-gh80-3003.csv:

Comment,Designator,Footprint,LCSC,Quantity
1k,"R4,R7",R_0402_1005Metric,C11702,2
100nF,"C12,C13,C14,C15,C16,C17,C18,C5,C8,C9",C_0402_1005Metric,C1525,10
10uF,C10,C_0402_1005Metric,C15525,1
22pF,"C2,C3",C_0402_1005Metric,C1555,2
Conn_01x04_MountingPin,J3,JST_SH_SM04B-SRSS-TB_1x04-1MP_P1.00mm_Horizontal,C160404,1
USB_C,J4,USB_C_Receptacle_HRO_TYPE-C-31-M-12,C165948,1
1k,"R106,R107,R108,R5,R6",R_0805_2012Metric,C17513,5
22,R100,R_0805_2012Metric,C17561,1
RP2040,U2,RP2040-QFN-56,C2040,1
D_Small,"D1,D10,D100,D101,D102,D103,D104,D105,D106,D107,D11,D110,D111,D112,D113,D114,D115,D116,D117,D118,D119,D121,D122,D124,D126,D127,D128,D129,D13,D130,D131,D14,D15,D16,D17,D18,D19,D2,D20,D21,D22,D24,D25,D26,D27,D29,D3,D30,D31,D32,D35,D37,D38,D39,D4,D40,D41,D42,D43,D44,D45,D46,D47,D48,D49,D5,D50,D51,D52,D53,D54,D55,D57,D58,D59,D6,D60,D61,D62,D63,D64,D65,D66,D67,D68,D69,D7,D70,D71,D72,D73,D74,D75,D76,D77,D78,D79,D8,D80,D81,D82,D83,D84,D85,D86,D87,D88,D89,D9,D90,D91,D92,D93,D94,D95,D96,D97,D98,D99",D_SOD-123,C2099,119
27R,"R2,R3",R_0603_1608Metric,C25190,2
5.1k,"R22,R8",R_0402_1005Metric,C25905,2
0.1uF,C1,C_0805_2012Metric,C49678,1
1uF,"C11,C4,C6,C7",C_0402_1005Metric,C52923,4
XC6206,U5,SOT-23,C5446,1
500mA,"F1,F2",Fuse_1206_3216Metric,C70076,2
SRV05-4,U3,SOT-23-6-routable,C85364,1
12MHz,Y1,Crystal_SMD_3225-4Pin_3.2x2.5mm,C9002,1
W25Q128JVS,U4,SOIC-8_5.23x5.23mm_P1.27mm,C97521,1

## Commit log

2026-02-07 push
2026-02-07 finished production files
2026-02-12 push firmware
2026-02-12 add license form sorce
2026-02-12 add prebuilt
